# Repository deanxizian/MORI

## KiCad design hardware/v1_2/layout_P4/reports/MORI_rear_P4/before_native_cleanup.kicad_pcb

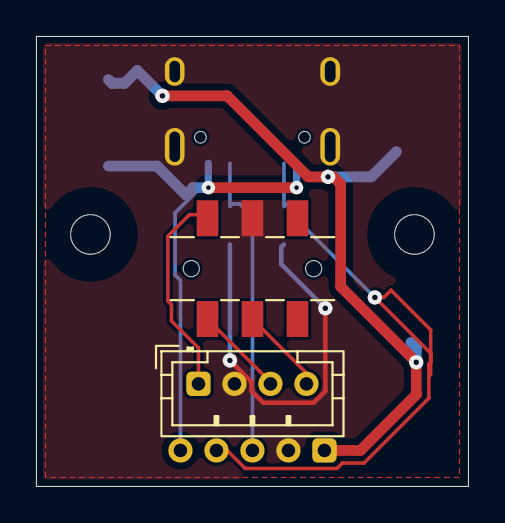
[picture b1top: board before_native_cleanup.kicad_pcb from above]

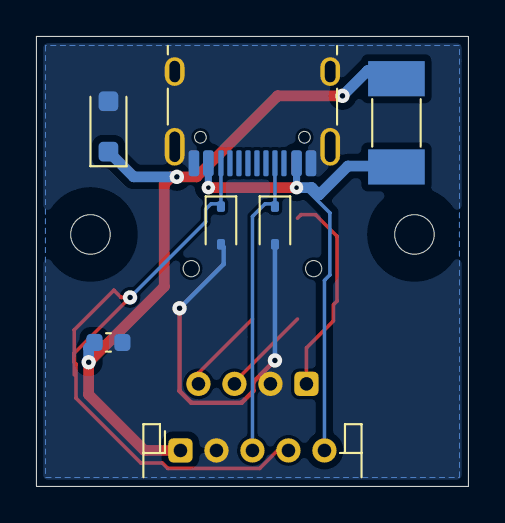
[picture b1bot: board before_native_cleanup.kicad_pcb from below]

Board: 2 copper layers, 24.0 x 25.0 mm, 11 parts (7 on the bottom side), 8 nets.

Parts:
C1: 100n / 50V / X7R; C_0603_1608Metric
D1: SMF24A / Littelfuse; D_SOD-123F
D2, D3: PESD5V0L1BA,115; D_SOD-323
F1: 045101.5MRL / 1.5A; Littelfuse_451_6.1x2.69_P4__P3R1_F1
H1, H2: M2 clearance; MountingHole_2.2mm_M2
J2: CHARGER / PH5 SIDE ENTRY; JST_PH_S5B-PH-K_1x05_P2.00mm_Horizontal__P4_ANNULUS__P3R1_J2
J3: MASTER + DISARM / PH4; JST_PH_B4B-PH-K_1x04_P2.00mm_Vertical__P4_ANNULUS
SW1: SOFNG MS-202V-G3; SOFNG_MS202V_G3_P4__P3R1_SW1
USB1: HRO TYPE-C-31-M-12 / charge only; USB_C_Receptacle_HRO_TYPE-C-31-M-12__P4_ANNULUS__P3R1_USB1

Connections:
/CC1: D2.1, J2.3, USB1.A5
/CC2: D3.1, J2.4, USB1.B5
/CLR_N: J3.4, SW1.5
/GND: C1.2, D1.2, D2.2, D3.2, J2.2, J3.2, SW1.2, USB1.A1, USB1.A12, USB1.B1, USB1.B12, USB1.SH
/LOOP_3V3: J3.3, SW1.4
/MASTER_RETURN: J3.1, SW1.1
/VBUS_FUSED: C1.1, D1.1, F1.2, J2.1
/VBUS_RAW: F1.1, J2.5, USB1.A4, USB1.A9, USB1.B4, USB1.B9

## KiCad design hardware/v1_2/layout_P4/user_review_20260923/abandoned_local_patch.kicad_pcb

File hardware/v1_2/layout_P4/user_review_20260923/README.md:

# P4 用户圈选复核与整改

状态：**FAIL**。保留 `before/` 原生项目快照和 `baseline.json` 哈希。

已确认前次附加审查漏掉最短拓扑、抖动、短折返与完整引脚逃线。对面铜层和连接器自身网络不能自动放行；这属于工程要求未满足，并非只等待用户审美确认。

圈选涉及 ARM_CLK、LINK_RX、5V_MOTION／FAULT_N 和 ARM_Q。坐标与失效项见 `review.json`，原生走线与焊盘记录见 `motion_geometry_before.json`。整改进行中；尚不声称已全部修复。

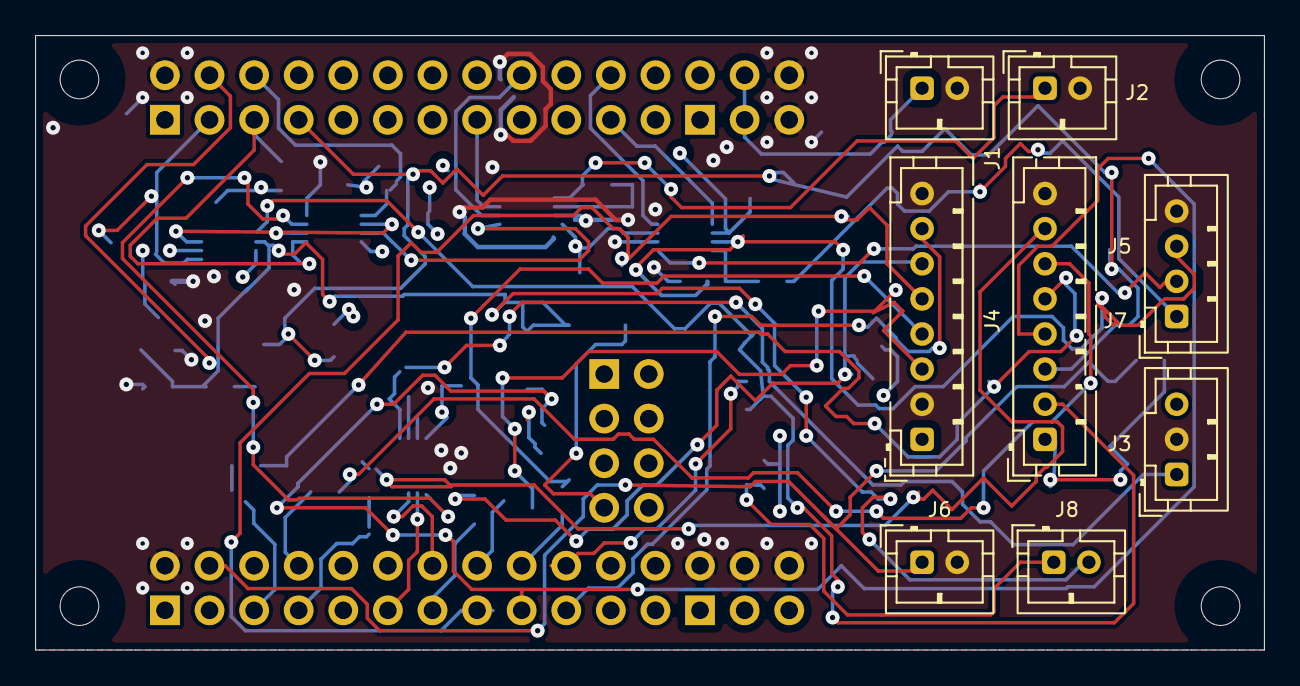
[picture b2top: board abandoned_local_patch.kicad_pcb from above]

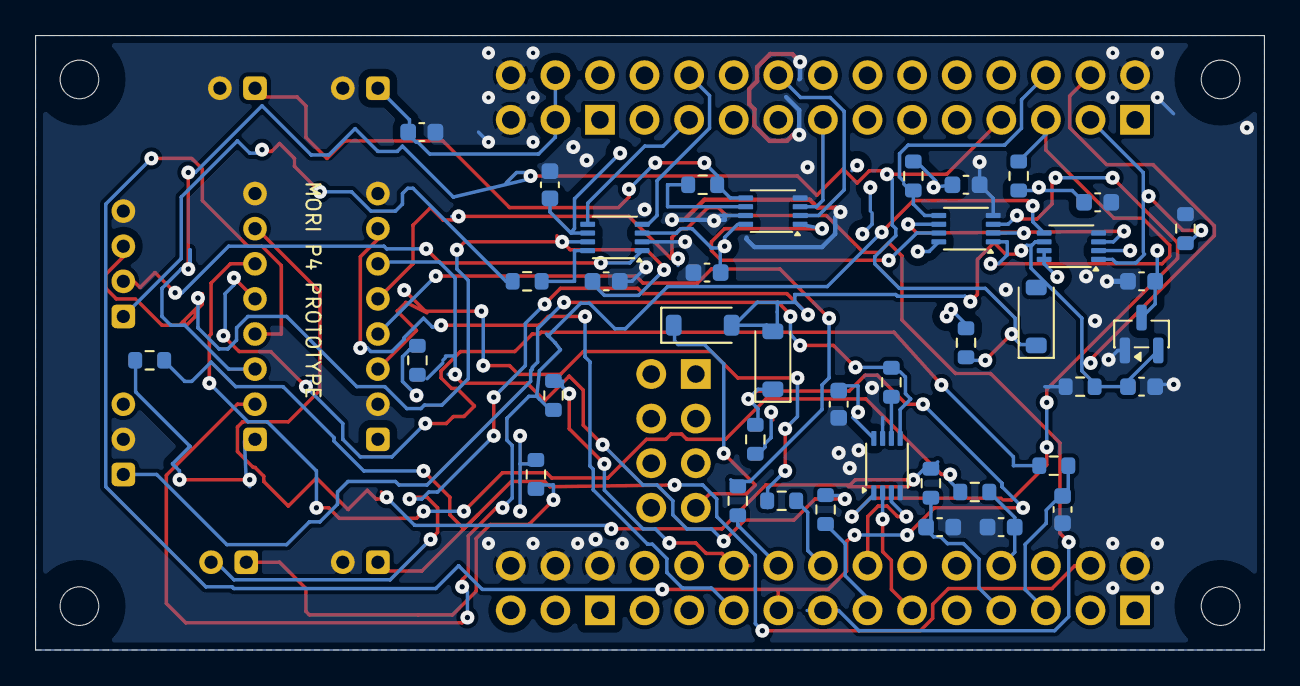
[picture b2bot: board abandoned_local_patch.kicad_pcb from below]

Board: 4 copper layers, 70.0 x 35.0 mm, 53 parts (40 on the bottom side), 45 nets.

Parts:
C1, C2, C3, C4, C5, C6, C7, C12: 100n; C_0603_1608Metric
C8: 10u; C_0603_1608Metric
C9, C10, C11: 10n; C_0603_1608Metric
D1, D2, D3: BAT54H,115; D_SOD-123
H1, H2, H3, H4: M2 clearance; MountingHole_2.2mm_M2
J1: MOTION 5V IN; JST_PH_B2B-PH-K_1x02_P2.00mm_Vertical__P4_PH_ANNULUS
J2: S288 DATA ONLY; JST_PH_B2B-PH-K_1x02_P2.00mm_Vertical__P4_PH_ANNULUS
J3: HEAD DATA ONLY; JST_PH_B3B-PH-K_1x03_P2.00mm_Vertical__P4_PH_ANNULUS
J4: BODY IMU SPI; JST_PH_B8B-PH-K_1x08_P2.00mm_Vertical__P4_PH_ANNULUS__P3R1_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
J5: CAM J11 MATCH; JST_PH_B4B-PH-K_1x04_P2.00mm_Vertical__P4_PH_ANNULUS
J6: INTERNAL SERVICE KEY; JST_PH_B2B-PH-K_1x02_P2.00mm_Vertical__P4_PH_ANNULUS
J7: POWER CONTROL; JST_PH_B8B-PH-K_1x08_P2.00mm_Vertical__P4_PH_ANNULUS__P3R1_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
J8: LATCHED ENABLE LOOP; JST_PH_B2B-PH-K_1x02_P2.00mm_Vertical__P4_PH_ANNULUS
R1, R2: 68; R_0603_1608Metric
R3, R4, R5, R7, R8, R13, R17, R18: 10k; R_0603_1608Metric
R6, R14, R15, R16, R19: 1k; R_0603_1608Metric
R9: 47; R_0603_1608Metric
R10, R11, R12: 33; R_0603_1608Metric
U1, U2: SN74LVC2G125DCUR; TI_DCU0008A_0p85x0p30
U3: SN74LVC2G32DCUR; TI_DCU0008A_0p85x0p30
U4: TXU0202DCUR; TI_DCU0008A_0p85x0p30
U5: SN74LVC1G74DCUR; TI_DCU0008A_0p85x0p30
U6: TLV803EA29DBZR; SOT-23
U100: WeAct STM32F412RET6 64Pin V1.1; WeAct_F4_64Pin_V11

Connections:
/+3V3: C1.1, C2.1, C3.1, C4.1, C5.1, C6.1, J4.1, J7.1, R3.2, R4.2, R6.1, R8.2, R13.2, R17.2, R18.2, U1.8, U2.8, U3.8, U4.3, U4.6, U5.2, U5.7, U5.8, U6.3, U100.C1, U100.C3, U100.C5
/+5V_MOTION: C8.1, J1.1, U100.D3, U100.D4
/ARM_CLK: R5.1, U5.1, U100.B3
/ARM_FEEDBACK: R19.2, U100.A20
/ARM_Q: J7.2, R19.1, U5.5
/ARM_Q_N: U3.2, U3.6, U5.3
/BAT_ADC: C9.1, R14.2, U100.A5
/BAT_ADC_IN: J7.5, R14.1
/CAM_3V3: C7.1, J5.3, U4.7
/CAM_RX: J5.1, R9.2
/CAM_RX_BUF: R9.1, U4.8
/CAM_TX: J5.2, U4.1
/CHG_N: D3.1, J7.4, R18.1, U100.A17
/CLR_N: C12.1, D1.2, D2.2, D3.2, J8.2, R7.1, U5.6, U6.2, U100.B4
/CURRENT_ADC: C11.1, R16.2, U100.A7
/CURRENT_ADC_IN: J7.7, R16.1
/FAULT_N: D2.1, J7.3, R17.1, U100.B7
/GND: C1.2, C2.2, C3.2, C4.2, C5.2, C6.2, C7.2, C8.2, C9.2, C10.2, C11.2, C12.2, J1.2, J2.2, J3.2, J4.2, J4.8, J5.4, J6.2, J7.8, R5.2, R7.2, U1.4, U1.7, U2.4, U2.7, U3.4, U4.2, U5.4, U6.1, U100.A2, U100.B2, U100.C2, U100.C4, U100.C6, U100.D5, U100.D6
/HEAD_BUS: J3.1, R2.2, U2.5
/HEAD_OE_N: U2.1, U3.3
/HEAD_OE_REQ_N: R4.1, U3.5, U100.B6
/HEAD_RX: U2.3, U100.A14
/HEAD_TX: U2.2, U100.A11
/HEAD_TX_BUF: R2.1, U2.6
/IMU_CS: J4.6, R12.2, R13.1
/IMU_CS_M: R12.1, U100.A13
/IMU_DRDY: J4.7, U100.A19
/IMU_MISO: J4.5, U100.A15
/IMU_MOSI: J4.4, R11.2
/IMU_MOSI_M: R11.1, U100.A18
/IMU_SCK: J4.3, R10.2
/IMU_SCK_M: R10.1, U100.A16
/LINK_RX: U4.4, U100.B22
/LINK_TX: U4.5, U100.B21
/LOOP_3V3: J8.1, R6.2
/NRST: D1.1, U100.E7
/S288_BUS: J2.1, R1.2, U1.5
/S288_OE_N: U1.1, U3.7
/S288_OE_REQ_N: R3.1, U3.1, U100.B5
/S288_RX: U1.3, U100.B15
/S288_TX: U1.2, U100.B18
/S288_TX_BUF: R1.1, U1.6
/USER_KEY_N: J6.1, R8.1, U100.A4
/WHEEL_ADC: C10.1, R15.2, U100.A8
/WHEEL_ADC_IN: J7.6, R15.1

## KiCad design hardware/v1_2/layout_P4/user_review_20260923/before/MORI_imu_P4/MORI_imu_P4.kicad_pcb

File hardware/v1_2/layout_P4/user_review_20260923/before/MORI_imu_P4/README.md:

# MORI_imu_P4

PROTOTYPE / 实物 NOT_TESTED。尺寸 20×16×1.6 mm，2 层。

KiCad 10.0.6：ERC 0，DRC 0，未连接 0，原理图一致性 0。报告是否对应当前文件：是。

原生 `.kicad_pro`、`.kicad_sch`、`.kicad_pcb` 均在本目录。资料请看 `../../layout_P4/README.md` 和 `../../layout_P4/接插件与充电接口说明.md`。这是设计检查结果，不是热、电池、动态平衡、EMC 或生产认证。没有下单；没有制造数据导出。

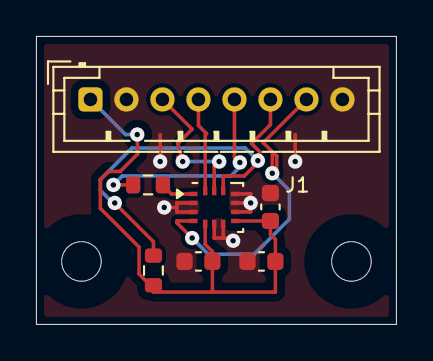
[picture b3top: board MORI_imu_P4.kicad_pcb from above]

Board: 2 copper layers, 20.0 x 16.0 mm, 9 parts (0 on the bottom side), 8 nets.

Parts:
C1: 100n; C_0603_1608Metric
C2: 2.2u; C_0603_1608Metric
C3: 10n; C_0603_1608Metric
H1, H2: M2 clearance; MountingHole_2.2mm_M2
J1: BODY RIGID IMU; JST_PH_B8B-PH-K_1x08_P2.00mm_Vertical__P4_PH_ANNULUS__P3R1_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
R1: 33; R_0603_1608Metric
R2: 10k; R_0603_1608Metric
U1: ICM-42688-P; TDK_ICM42688P_LGA14_3x2p5__P2_U1__P3R1_U1

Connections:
/+3V3: C1.1, C2.1, C3.1, J1.1, R2.2, U1.5, U1.8
/CS_N: J1.6, R2.1, U1.12
/DRDY: J1.7, U1.4
/GND: C1.2, C2.2, C3.2, J1.2, J1.8, U1.2, U1.3, U1.6, U1.7, U1.9, U1.10, U1.11
/MISO: J1.5, R1.2
/MISO_IC: R1.1, U1.1
/MOSI: J1.4, U1.14
/SCK: J1.3, U1.13

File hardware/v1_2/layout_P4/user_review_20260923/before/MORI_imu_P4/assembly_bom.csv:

ref,value,footprint,source,note
U1,ICM-42688-P,MORI_Custom:TDK_ICM42688P_LGA14_3x2p5__P2_U1__P3R1_U1,https://www.lcsc.com/datasheet/C1850418.pdf,Prototype based on vendor DS-000347 pinout. No raw cell welding; IC requires reflow. Assembly pad review required.
J1,BODY RIGID IMU,MORI_Custom:JST_PH_B8B-PH-K_1x08_P2.00mm_Vertical__P4_PH_ANNULUS__P3R1_J1,https://www.jst-mfg.com/product/pdf/eng/ePH.pdf,P4 PH 2.0 mm. PHR-8 / SPH-002T-P0.5S. Signal pin numbering unchanged. Check both mating views; never wire by color alone.
C1,100n,Capacitor_SMD:C_0603_1608Metric,,
C2,2.2u,Capacitor_SMD:C_0603_1608Metric,,
C3,10n,Capacitor_SMD:C_0603_1608Metric,,
R1,33,Resistor_SMD:R_0603_1608Metric,,
R2,10k,Resistor_SMD:R_0603_1608Metric,,
H1,M2 clearance,MountingHole:MountingHole_2.2mm_M2,,
H2,M2 clearance,MountingHole:MountingHole_2.2mm_M2,,

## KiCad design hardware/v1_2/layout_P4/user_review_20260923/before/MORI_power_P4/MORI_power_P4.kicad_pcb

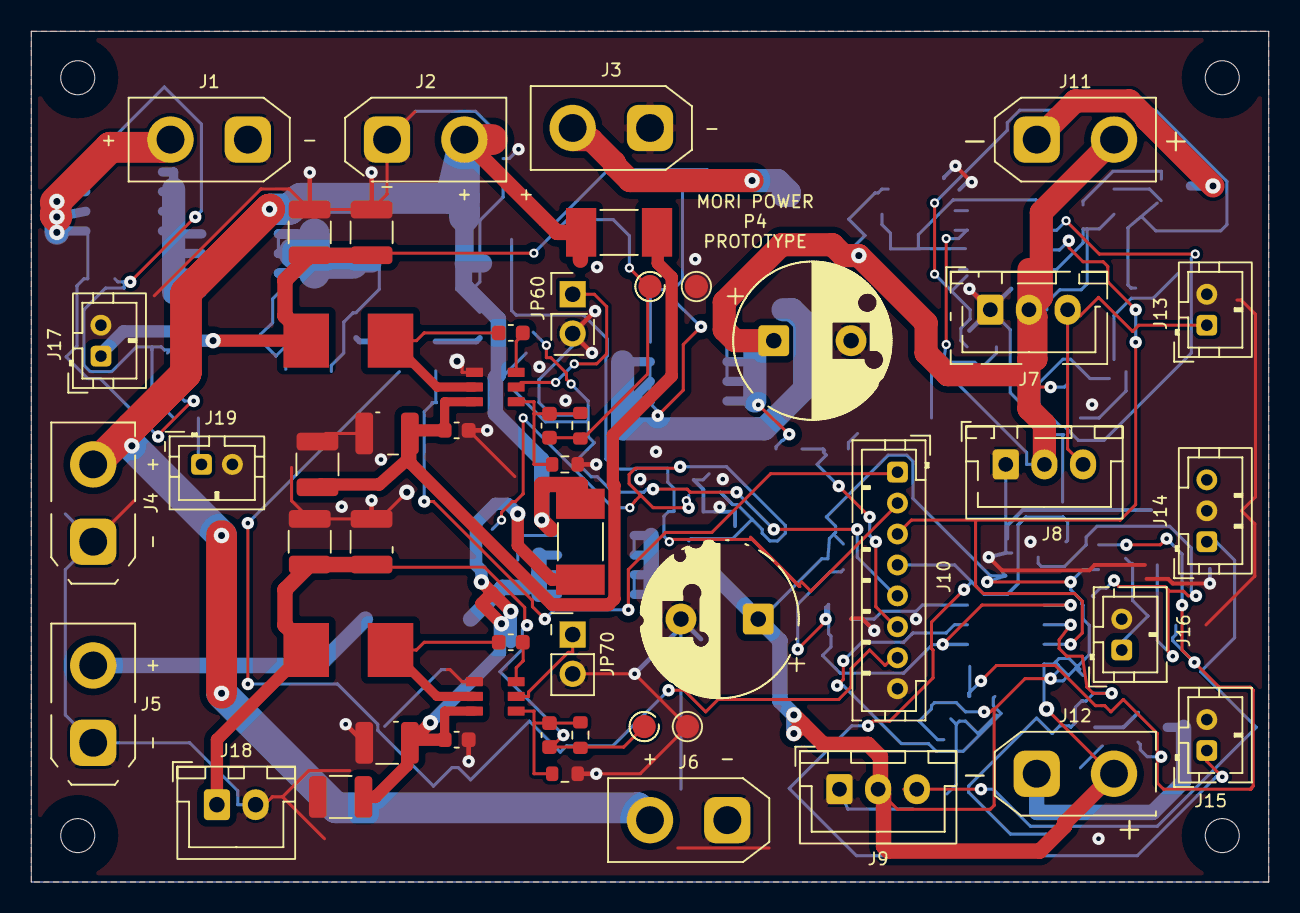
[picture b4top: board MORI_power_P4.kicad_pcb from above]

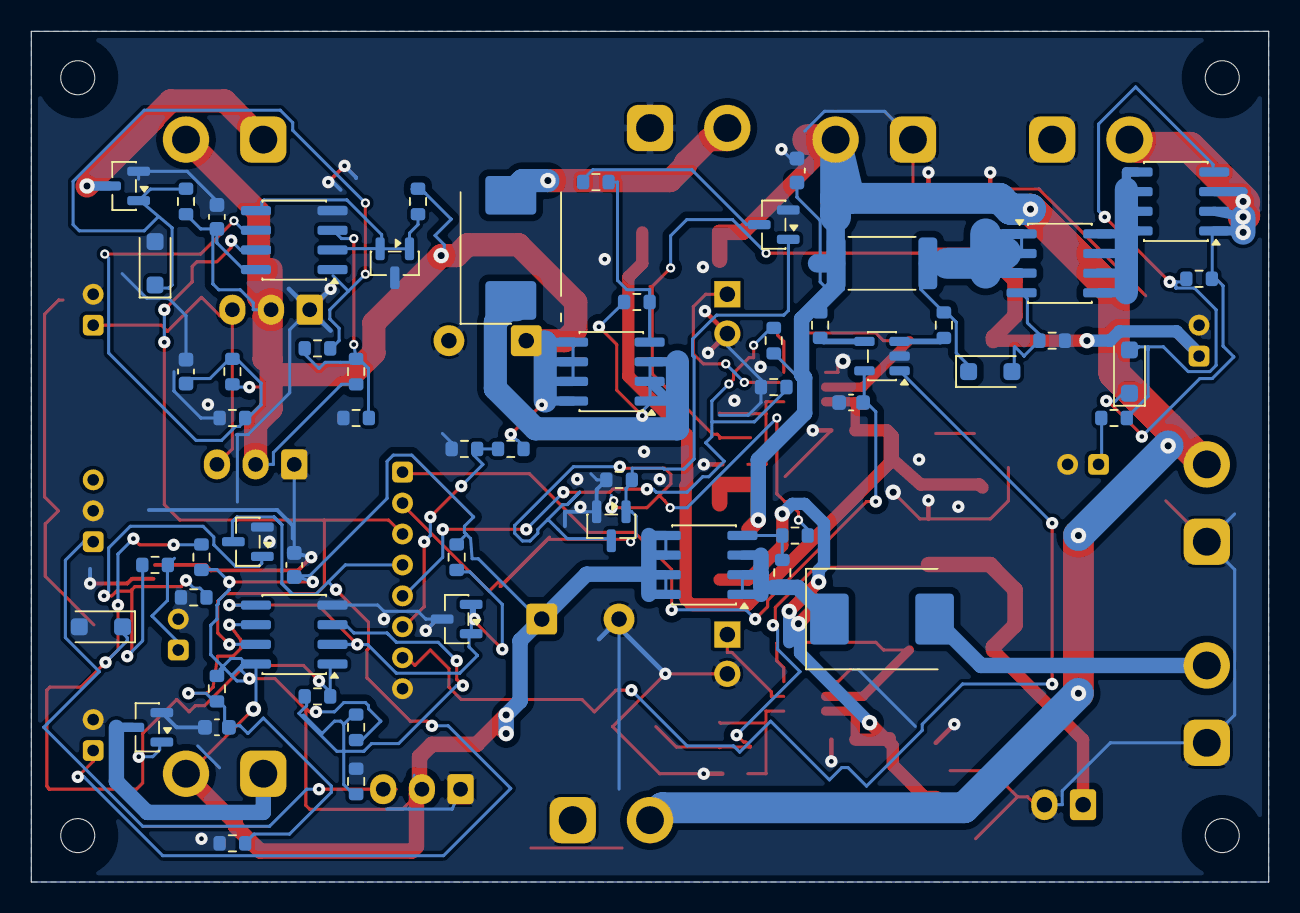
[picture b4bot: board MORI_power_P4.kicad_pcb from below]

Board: 2 copper layers, 80.0 x 55.0 mm, 112 parts (57 on the bottom side), 53 nets.

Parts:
C1, C20, C40: 100n; C_0603_1608Metric
C2: 1u 25V; C_0603_1608Metric__P3_C2
C10: Panasonic EEU-FR1C102 1000uF 16V; CP_Radial_D10.0mm_P5.00mm__P2_C10__P3_C10__P3R1_C10
C21, C41: 10n; C_0603_1608Metric
C30: Panasonic EEU-FR1C102 1000uF 16V; CP_Radial_D10.0mm_P5.00mm__P3_C30__P3R1_C30
C60: 22u / 25V / X7R; C_1210_3225Metric__P3_C60__P3R1_C60
C61, C62, C71, C72: 100n / 50V / X7R; C_0603_1608Metric
C63, C64, C66, C73, C76: 22u / 25V / X7R; C_1210_3225Metric
C65: 75p / 50V / C0G; C_0603_1608Metric
C70: 22u / 25V / X7R; C_1210_3225Metric__P3_C70
C74: 22u / 25V / X7R; C_1210_3225Metric__P3_C74
C75: 75p / 50V / C0G; C_0603_1608Metric__P3R1_C75
D1, D20, D40, D90: BZT52H-C10,115; D_SOD-123F
D10: B540C-13-F; D_SMC__P3_D10__P3R1_D10
D30: B540C-13-F; D_SMC
F60: 1A / 125V / very fast; Fuse_Littelfuse-NANO2-451_453
F70: 2A / 125V / very fast; Fuse_Littelfuse-NANO2-451_453
H1, H2, H3, H4: M2 mounting / POSITION TBD; MountingHole_2.2mm_M2
J1: PACK AFTER 6.3A FUSE; AMASS_XT30UPB-M_1x02_P5.0mm_Vertical__P3_J1
J2: WHEEL BUCK VIN; AMASS_XT30UPB-M_1x02_P5.0mm_Vertical__P3_J2__P3R1_J2
J3: WHEEL BUCK 9V RETURN; AMASS_XT30UPB-M_1x02_P5.0mm_Vertical__P3R1_J3
J4: HEAD BUCK VIN; AMASS_XT30UPB-M_1x02_P5.0mm_Vertical__P2_J4__P3_J4__P3R1_J4
J5: HEAD BUCK 6V RETURN; AMASS_XT30UPB-M_1x02_P5.0mm_Vertical__P2_J5__P3_J5
J6: RAW BAT SERVICE / DNP; AMASS_XT30UPB-M_1x02_P5.0mm_Vertical__P3_J6__P3R1_J6
J7: S288 L; JST_XH_B3B-XH-A_1x03_P2.50mm_Vertical__P2_J7__P3_J7__P3R1_J7
J8: S288 R; JST_XH_B3B-XH-A_1x03_P2.50mm_Vertical__P2_J8__P3R1_J8
J9: SCS0009 CHAIN; JST_XH_B3B-XH-A_1x03_P2.50mm_Vertical
J10: MOTION CONTROL; JST_PH_B8B-PH-K_1x08_P2.00mm_Vertical__P4_PH_ANNULUS__P3R1_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
J11: WHEEL DUMP 5R6 EXTERNAL; AMASS_XT30UPB-M_1x02_P5.0mm_Vertical
J12: HEAD DUMP 10R EXTERNAL; AMASS_XT30UPB-M_1x02_P5.0mm_Vertical__P2_J12__P3R1_J12
J13: S288 DATA; JST_PH_B2B-PH-K_1x02_P2.00mm_Vertical__P4_PH_ANNULUS
J14: HEAD DATA; JST_PH_B3B-PH-K_1x03_P2.00mm_Vertical__P4_PH_ANNULUS
J15: CHARGE INTERLOCK; JST_PH_B2B-PH-K_1x02_P2.00mm_Vertical__P4_PH_ANNULUS__P3R1_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
J16: CHARGER RAW VBUS SENSE; JST_PH_B2B-PH-K_1x02_P2.00mm_Vertical__P4_PH_ANNULUS__P3R1_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
J17: MOTION 5V OUT / 1+ 2GND; JST_PH_B2B-PH-K_1x02_P2.00mm_Vertical__P4_PH_ANNULUS
J18: CAM 5V OUT / 1+ 2GND; JST_XH_B2B-XH-A_1x02_P2.50mm_Vertical
J19: REAR MASTER / 1RETURN 2GND; JST_PH_B2B-PH-K_1x02_P2.00mm_Vertical__P4_PH_ANNULUS__P3R1_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
JP60: SERVICE OFF / OPEN=ON; PinHeader_1x02_P2.54mm_Vertical__P3_JP60__P3R1_JP60
JP70: SERVICE OFF / OPEN=ON; PinHeader_1x02_P2.54mm_Vertical__P3R1_JP70
L60, L70: 10uH / SRP7050TA-100M; Bourns_SRP7050TA_8p4_span_2p5_gap
Q1, Q10, Q30, Q90: AO4407A; SOIC-8_3.9x4.9mm_P1.27mm
Q11, Q20, Q31, Q40: AO3400A; SOT-23
Q50: MMBT3904LT1G; SOT-23
R1, R10, R30, R54, R91: 10k; R_0603_1608Metric
R2: WSL2512R0100FEA 10mR 1% 1W; R_2512_6332Metric
R3, R4: 0; R_0603_1608Metric
R11, R31: 100; R_0603_1608Metric
R20, R24, R40, R44: 2.2k; R_0603_1608Metric
R21: 33.2k 0.1%; R_0603_1608Metric
R22, R26, R42, R46: 10k 0.1%; R_0603_1608Metric
R23, R43: 1M 0.1%; R_0603_1608Metric
R25: 37.4k 0.1%; R_0603_1608Metric
R41: 16.5k 0.1%; R_0603_1608Metric
R45: 18.7k 0.1%; R_0603_1608Metric
R50, R52: 100k 0.1%; R_0603_1608Metric
R51, R53: 27k 0.1%; R_0603_1608Metric
R55: 47k; R_0603_1608Metric
R56, R90: 100k; R_0603_1608Metric
R60, R70: 100k / 0.1%; R_0603_1608Metric
R61: 13.3k / 0.1%; R_0603_1608Metric
R71: 13.3k / 0.1%; R_0603_1608Metric__P3_R71
TP60: +5V_MOTION; TestPoint_Pad_D1.5mm__P3_TP60
TP61, TP71: GND; TestPoint_Pad_D1.5mm
TP70: +5V_CAM; TestPoint_Pad_D1.5mm__P3R1_TP70
U1: INA180A1IDBVR; SOT-23-5
U20, U40: LM393BDR; SOIC-8_3.9x4.9mm_P1.27mm
U21, U41: TL431BIDBZR; SOT-23
U60, U70: TPS54302DDCR; TI_DDC0006A_TPS54302

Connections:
/+3V3: C1.1, J10.1, U1.5
/+5V_CAM: C73.1, C74.1, C75.1, J18.1, L70.2, R70.1, TP70.1
/+5V_MOTION: C63.1, C64.1, C65.1, J17.1, L60.2, R60.1, TP60.1
/ARM_Q: J10.2, Q11.1, Q31.1, R54.1
/BAT_ADC: J10.5, R50.2, R51.1
/BAT_IN: Q1.5, Q1.6, Q1.7, Q1.8, Q90.5, Q90.6, Q90.7, Q90.8
/BAT_MON: C2.1, F60.1, F70.1, J2.2, J4.2, J6.2, R2.2, R4.1, R50.1
/BAT_REV: D1.1, Q1.1, Q1.2, Q1.3, R2.1, R3.1
/C5_BOOT: C72.1, U70.6
/C5_EN: JP70.1, U70.5
/C5_FB: C75.2, R70.2, R71.1, U70.4
/C5_SW: C72.2, L70.1, U70.2
/C5_VIN: C70.1, C71.1, C76.1, F70.2, U70.3
/CHG_BASE: Q50.1, R55.2, R56.1
/CHG_N: J10.4, J15.1, Q50.3
/CURRENT_ADC: J10.7, U1.1
/FAULT_N: J10.3, U20.7, U40.7
/GND: C1.2, C2.2, C10.2, C20.2, C21.2, C30.2, C40.2, C41.2, C60.2, C61.2, C63.2, C64.2, C66.2, C70.2, C71.2, C73.2, C74.2, C76.2, D20.2, D40.2, J1.1, J2.1, J3.1, J4.1, J5.1, J6.1, J7.1, J8.1, J9.1, J10.8, J13.2, J14.2, J15.2, J16.2, J17.2, J18.2, J19.2, JP60.2, JP70.2, Q11.2, Q20.2, Q31.2, Q40.2, Q50.2, R1.2, R22.2, R26.2, R42.2, R46.2, R51.2, R53.2, R54.2, R56.2, R61.2, R71.2, TP61.1, TP71.1, U1.2, U20.4, U21.3, U40.4, U41.3, U60.1, U70.1
/H6_IN: D30.2, J5.2
/H_BRAKE_GATE: D40.1, Q40.1, R43.1, R44.2, U40.1
/H_BUS: J9.3, J14.1
/H_DUMP_D: J12.1, Q40.3
/H_GATE: Q30.4, R30.1, R31.1
/H_GATE_LOW: Q31.3, R31.2
/H_OVSENSE: C41.1, R45.2, R46.1, U40.6
/H_PRE: D30.1, Q30.1, Q30.2, Q30.3, R30.2
/H_REF: R40.2, U40.2, U40.5, U41.1, U41.2
/H_SENSE: R41.2, R42.1, R43.2, U40.3
/H_VM: C30.1, C40.1, J9.2, J12.2, Q30.5, Q30.6, Q30.7, Q30.8, R40.1, R41.1, R44.1, R45.1, U40.8
/KELVIN_N: R4.2, U1.4
/KELVIN_P: R3.2, U1.3
/M5_BOOT: C62.1, U60.6
/M5_EN: JP60.1, U60.5
/M5_FB: C65.2, R60.2, R61.1, U60.4
/M5_SW: C62.2, L60.1, U60.2
/M5_VIN: C60.1, C61.1, C66.1, F60.2, U60.3
/MASTER_GATE: D90.2, Q90.4, R90.2, R91.1
/MASTER_RETURN: J19.1, R91.2
/PACK_FUSED: D90.1, J1.2, Q90.1, Q90.2, Q90.3, R90.1
/REV_GATE: D1.2, Q1.4, R1.1
/VBUS_CHARGE: J16.1, R55.1
/W9_IN: D10.2, J3.2
/WHEEL_ADC: J10.6, R52.2, R53.1
/W_BRAKE_GATE: D20.1, Q20.1, R23.1, R24.2, U20.1
/W_BUS: J7.3, J8.3, J13.1
/W_DUMP_D: J11.1, Q20.3
/W_GATE: Q10.4, R10.1, R11.1
/W_GATE_LOW: Q11.3, R11.2
/W_OVSENSE: C21.1, R25.2, R26.1, U20.6
/W_PRE: D10.1, Q10.1, Q10.2, Q10.3, R10.2
/W_REF: R20.2, U20.2, U20.5, U21.1, U21.2
/W_SENSE: R21.2, R22.1, R23.2, U20.3
/W_VM: C10.1, C20.1, J7.2, J8.2, J11.2, Q10.5, Q10.6, Q10.7, Q10.8, R20.1, R21.1, R24.1, R25.1, R52.1, U20.8
